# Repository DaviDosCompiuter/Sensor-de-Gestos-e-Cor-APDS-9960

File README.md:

# Sensor-de-Gestos-e-Cor-APDS-9960
Esse Github objetiva aplicar os conhecimentos da disciplina de técnicas de prototipagem do Instituto Federal de Campina Grande para obtenção de nota

Descrição do projeto:

Sensor de Gestos e de Cor APDS-9960

O Sensor de Gestos e de Cor APDS-9960 é utilizado para fazer a medição de luz, cor ambiente, detecção de proximidade e detecção de gestos. O mesmo consegue fazer detecções numa faixa de 10 a 20cm.

Este Sensor de Gestos e de Cor APDS-9960 permite que um robô, computador ou plataforma microcontrolada possa ser controlado a partir de gestos direcionados (alto/baixo/esquerda/direita). O sensor utiliza tecnologia I2C para comunicação, possui pino de interrupção (INT) e um pino adicional (VL) para LED infravermelho.

O Sensor de Gestos e de Cor APDS-9960 é comumente utilizado em projetos com Arduino, NodeMCU ESP8266, Raspberry ou outras plataformas microcontroladas.

Como curiosidade o Sensor de Gestos e de Cor APDS-9960 é o mesmo utilizado no Samsung Galaxy S5.

Especificações e características:
```
Tensão de operação: 3.3V
Interface de comunicação: I2C
Faixa de detecção: 10 a 20cm
Detecções: gestos/luz/cor ambiente/proximidade
```

Datasheet:
"doc/Datasheet APDS-9960.pdf"

Aplicações:

Projetos com Arduino ou outras plataformas microcontroladas em que seja necessário detectar a direção de gestos, intensidade de luz ambiente, cor ambiente ou proximidade.

Proposta da prática:

Dispositivo que auxiliam pessoas com deficienca à pegar livros em uma biblioteca.

Lista dos itens necessários:
```
01 - Arduino
01 - Sensor de Gestos e de Cor APDS-9960
01 - ponte h L293D
02 - Motores
01 - Bateria
04 - Polias
01 - Garra
01 - Estrutura de Ferro
```

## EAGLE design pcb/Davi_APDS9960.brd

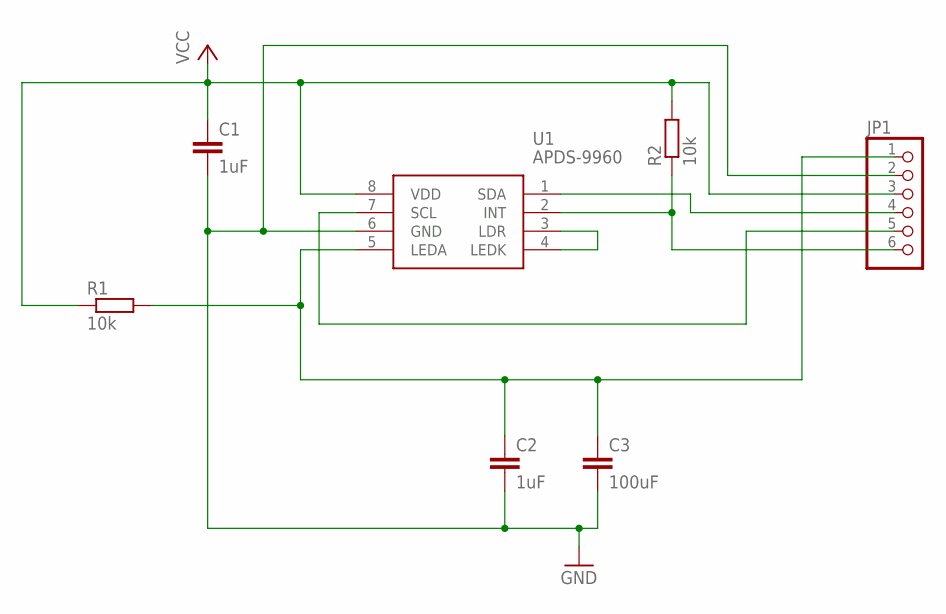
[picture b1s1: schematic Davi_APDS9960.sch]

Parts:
C1, C2: 1uF; C025-025X050
C3: 100uF; C025-025X050
JP1: PINHD-1X6; 1X06
R1, R2: 10k; 0207/7
U1: APDS-9960; APDS-9950

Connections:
GND: C1.2, C2.2, C3.2, JP1.2, U1.6 (GND)
unnamed: U1.3 (LDR), U1.4 (LEDK)
unnamed: C2.1, C3.1, JP1.1, R1.2, U1.5 (LEDA)
unnamed: JP1.6, R2.1, U1.2 (INT)
unnamed: JP1.4, U1.1 (SDA)
unnamed: JP1.5, U1.7 (SCL)
VCC: C1.1, JP1.3, R1.1, R2.2, U1.8 (VDD)

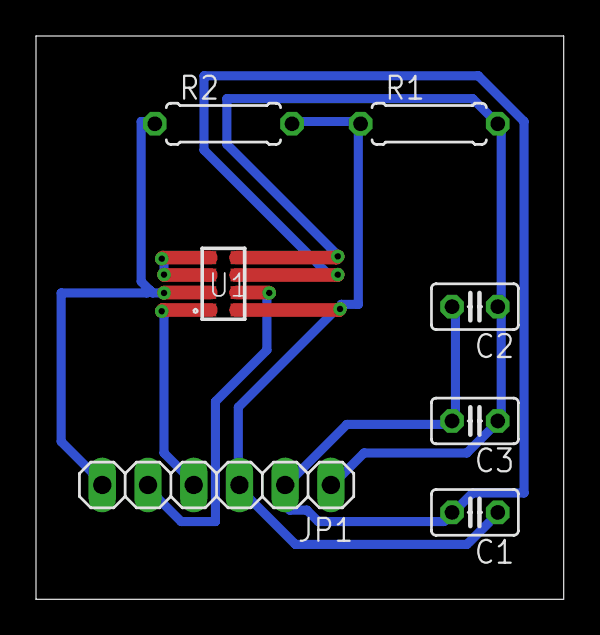
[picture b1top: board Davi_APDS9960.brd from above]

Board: 2 copper layers, 29.3 x 31.3 mm, 7 parts (0 on the bottom side), 7 nets.

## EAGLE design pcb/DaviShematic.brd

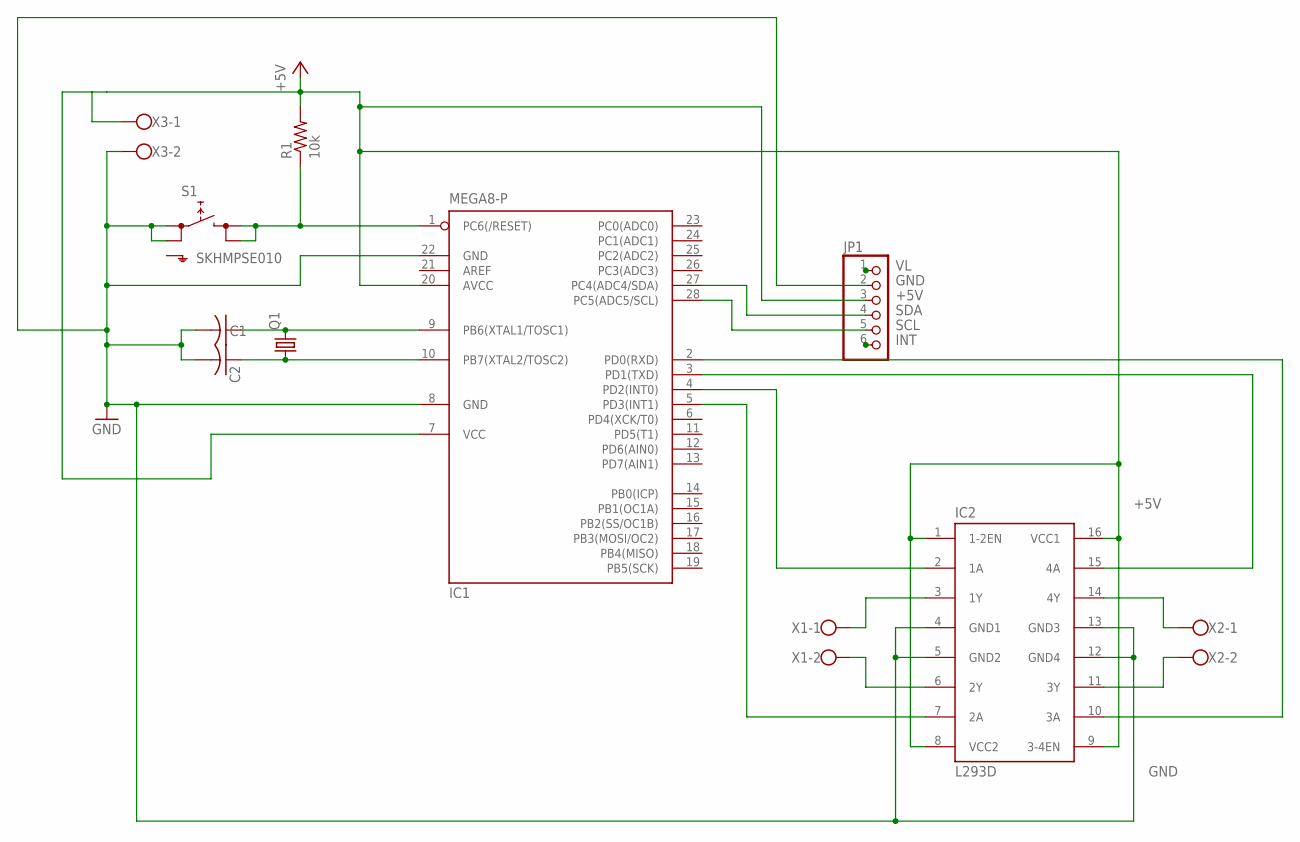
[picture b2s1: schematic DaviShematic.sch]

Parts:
C1, C2: C-US025-024X044; C025-024X044
IC1: MEGA8-P; DIL28-3
IC2: L293D; DIL16
JP1: PINHD-1X6; 1X06
Q1: CRYSTALHC49U-V; HC49U-V
R1: 10k; 0207/7
S1: SKHMPSE010; SKHMPXE010
X1, X2, X3: W237-102

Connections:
+5V: IC1.7 (VCC), IC1.20 (AVCC), IC2.1 (1-2EN), IC2.8 (VCC2), IC2.9 (3-4EN), IC2.16 (VCC1), JP1.3, R1.2, X3.1
GND: C1.2, C2.2, IC1.8 (GND), IC1.22 (GND), IC2.4 (GND1), IC2.5 (GND2), IC2.12 (GND4), IC2.13 (GND3), JP1.2, S1.1 (1.1), S1.2 (1.2), X3.2
INT: JP1.6
unnamed: IC1.1 (PC6(/RESET)), R1.1, S1.3 (2.1), S1.4 (2.2)
unnamed: C1.1, IC1.9 (PB6(XTAL1/TOSC1)), Q1.2
unnamed: C2.1, IC1.10 (PB7(XTAL2/TOSC2)), Q1.1
unnamed: IC2.3 (1Y), X1.1
unnamed: IC2.6 (2Y), X1.2
unnamed: IC2.14 (4Y), X2.1
unnamed: IC2.11 (3Y), X2.2
unnamed: IC1.4 (PD2(INT0)), IC2.2 (1A)
unnamed: IC1.5 (PD3(INT1)), IC2.7 (2A)
unnamed: IC1.3 (PD1(TXD)), IC2.15 (4A)
unnamed: IC1.2 (PD0(RXD)), IC2.10 (3A)
SCL: IC1.28 (PC5(ADC5/SCL)), JP1.5
SDA: IC1.27 (PC4(ADC4/SDA)), JP1.4
VL: JP1.1

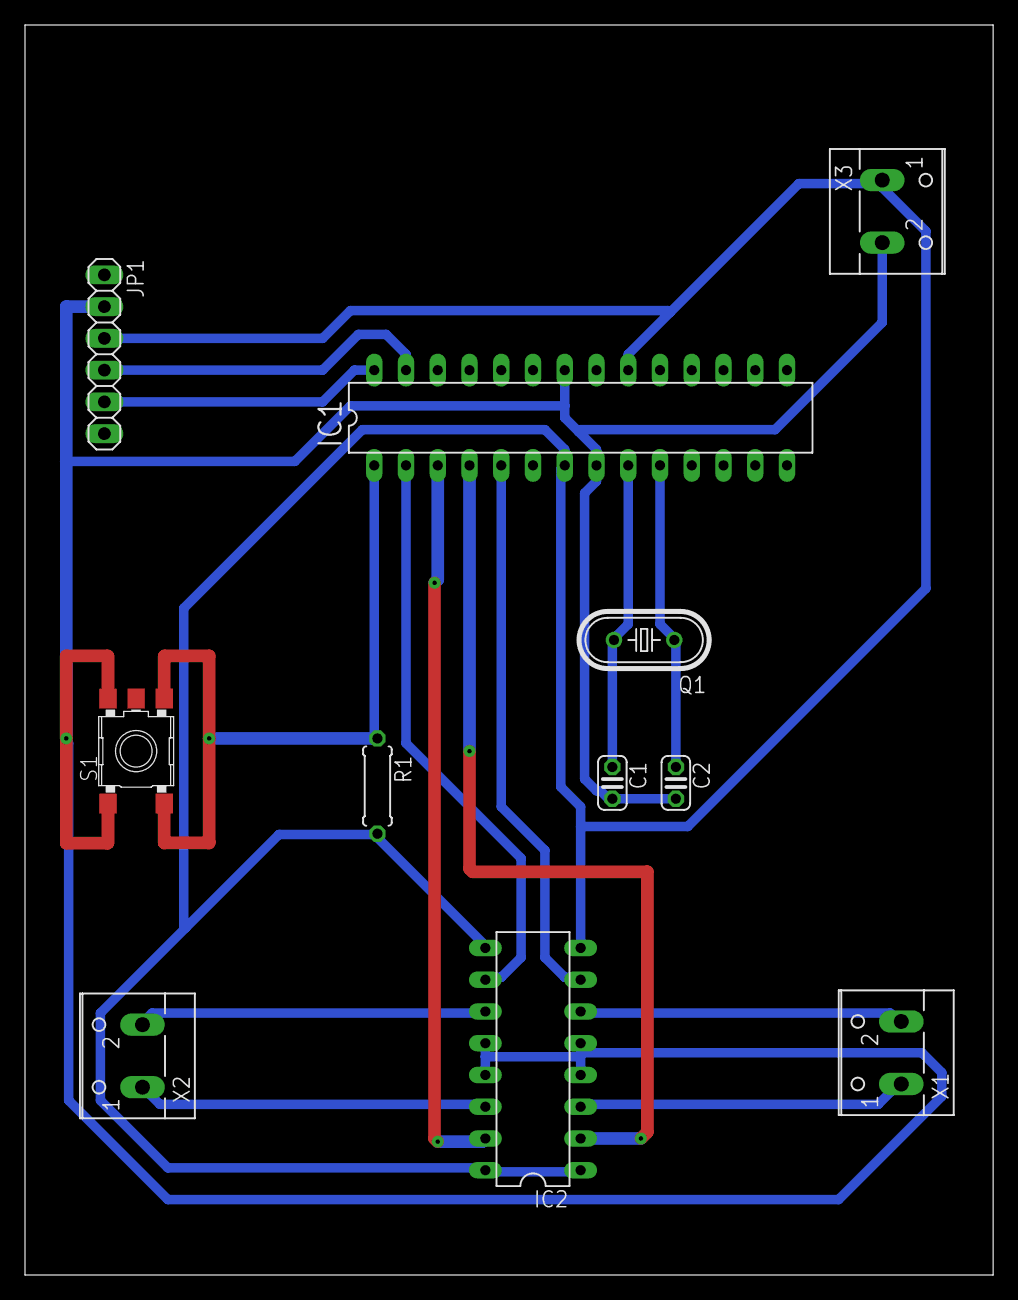
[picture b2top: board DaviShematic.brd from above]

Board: 2 copper layers, 77.5 x 100.0 mm, 11 parts (0 on the bottom side), 15 nets.
